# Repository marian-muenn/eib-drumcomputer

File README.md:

# EIB Drumcomputer

## Projektstruktur
~~~
Das Projekt ist wie folgt strukturiert:
  ./3d/                                                 Dateien für den 3D-Druck
  ./3d/abstandshalter_stromversorgung/                  Abstandhalter zur Montage der Stromversorgung
  ./3d/blindplatte/                                     Blindplatten in diversen Breiten
  ./3d/midi/                                            Frontplatte des MIDI-Interface-Moduls
  ./3d/modul-2-poti/                                    Frontplatte für Drummodule mit 2 Potentiometern
  ./3d/modul_3_poti/                                    Frontplatte für Drummodule mit 3 Potentiometern
  ./3d/winkel/                                          Winkel zur Platinenmontage
  ./doku/                                               Montageanleitung, Bauteillisten, Datenblätter und Spezifikationen
  ./kicad/                                              Platinenentwürfe
  ./kicad/midi-interface                                Platine des MIDI-Interface-Moduls
  ./kicad/line-out                                      Schaltplan des Line-Out Moduls
  ./kicad/klangerzeugung                                Platine zur Klangerzeugung
  ./ltspice/                                            Simulationen
  ./src                                                 Programmcode
  ./tex                                                 Latex Dokumente (Beleg und Montageanleitung)
~~~

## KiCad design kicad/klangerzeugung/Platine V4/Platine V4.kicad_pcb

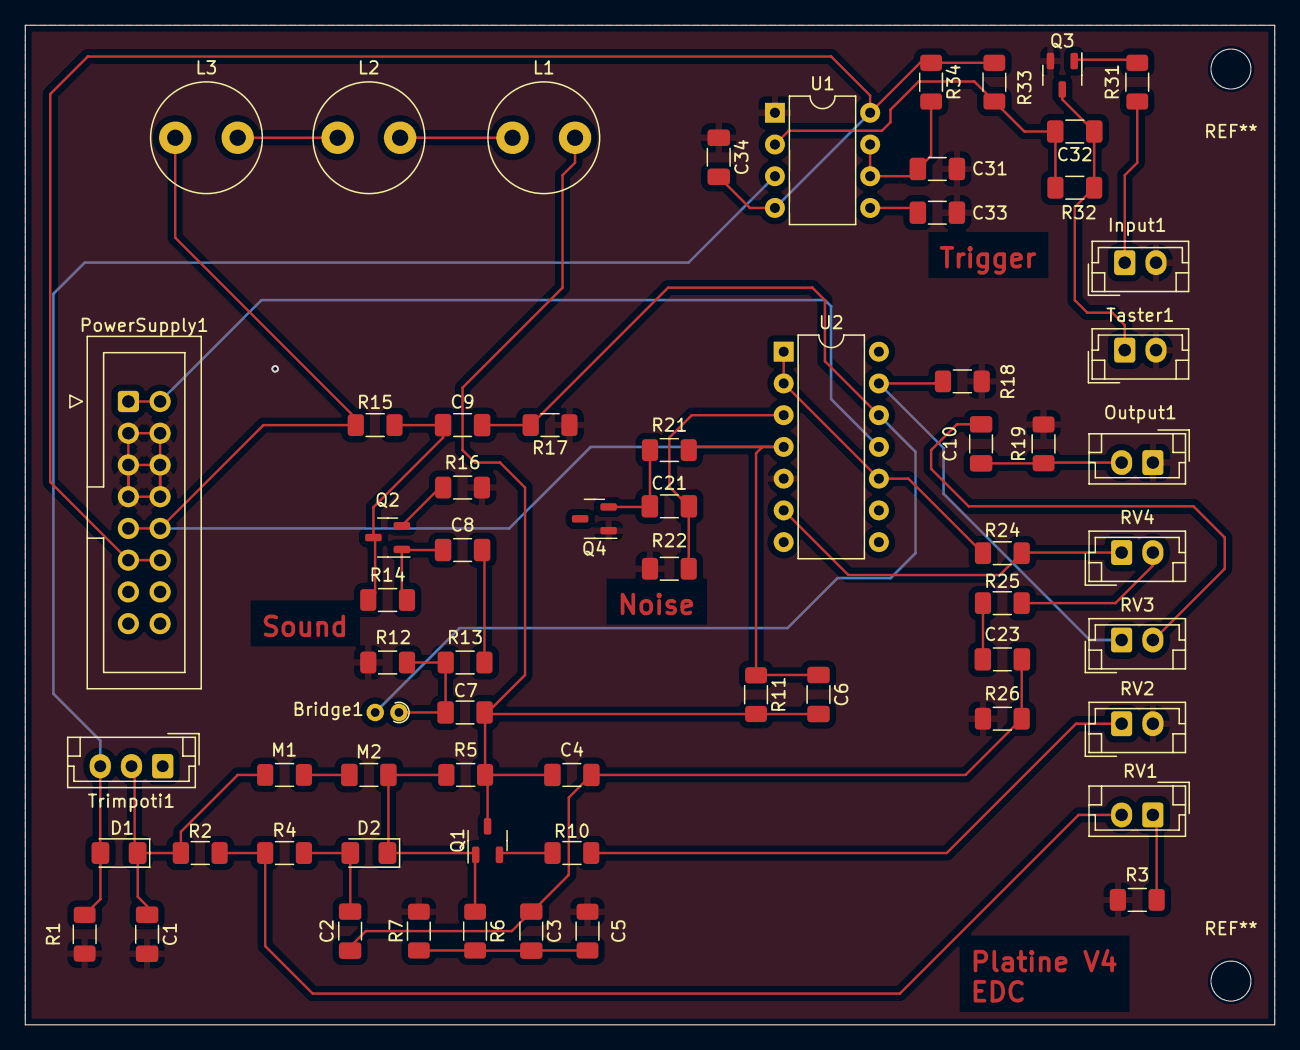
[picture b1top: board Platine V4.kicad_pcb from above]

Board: 2 copper layers, 100.0 x 80.0 mm, 65 parts (0 on the bottom side), 39 nets.

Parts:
Bridge1: 0; R_Axial_DIN0204_L3.6mm_D1.6mm_P1.90mm_Vertical
C1: 56n; C_1206_3216Metric_Pad1.33x1.80mm_HandSolder
C2, C4, C32: 10n; C_1206_3216Metric_Pad1.33x1.80mm_HandSolder
C3, C6: 1n; C_1206_3216Metric_Pad1.33x1.80mm_HandSolder
C5: 1000k; R_1206_3216Metric_Pad1.30x1.75mm_HandSolder
C7, C8, C9, C10, C21, C23: 1u; C_1206_3216Metric_Pad1.33x1.80mm_HandSolder
C31, C34: 100n; C_1206_3216Metric_Pad1.33x1.80mm_HandSolder
C33: 10u; C_1206_3216Metric_Pad1.33x1.80mm_HandSolder
D1: D; D_1206_3216Metric_Pad1.42x1.75mm_HandSolder
D2: D2; D_1206_3216Metric_Pad1.42x1.75mm_HandSolder
Input1: Conn_01x02_Pin; JST_EH_B2B-EH-A_1x02_P2.50mm_Vertical
L1, L2, L3: 100m; L_Radial_D8.7mm_P5.00mm_Fastron_07HCP
M1: 1M; R_1206_3216Metric_Pad1.30x1.75mm_HandSolder
M2: 82n; C_1206_3216Metric_Pad1.33x1.80mm_HandSolder
Output1: Conn_01x02_Pin; JST_EH_B2B-EH-A_1x02_P2.50mm_Vertical
PowerSupply1: Conn_02x08_Odd_Even; IDC-Header_2x08_P2.54mm_Vertical
Q1, Q2, Q3, Q4: Q_NPN_BEC; SOT-23-3
R1, R31, R34: 10k; R_1206_3216Metric_Pad1.30x1.75mm_HandSolder
R2, R3, R4, R7, R13, R14: 1000k; R_1206_3216Metric_Pad1.30x1.75mm_HandSolder
R5, R6: 470k; R_1206_3216Metric_Pad1.30x1.75mm_HandSolder
R10: 100; R_1206_3216Metric_Pad1.30x1.75mm_HandSolder
R11, R15: 1.5k; R_1206_3216Metric_Pad1.30x1.75mm_HandSolder
R12, R16, R17: 3k; R_1206_3216Metric_Pad1.30x1.75mm_HandSolder
R18, R19, R24, R26: 1k; R_1206_3216Metric_Pad1.30x1.75mm_HandSolder
R21, R22, R25: 100k; R_1206_3216Metric_Pad1.30x1.75mm_HandSolder
R32: 47k; R_1206_3216Metric_Pad1.30x1.75mm_HandSolder
R33: 220; R_1206_3216Metric_Pad1.30x1.75mm_HandSolder
RV1, RV2, RV4: 10k; JST_EH_B2B-EH-A_1x02_P2.50mm_Vertical
RV3: 50k; JST_EH_B2B-EH-A_1x02_P2.50mm_Vertical
Taster1: Conn_01x02_Pin; JST_EH_B2B-EH-A_1x02_P2.50mm_Vertical
Trimpoti1: 10k; JST_EH_B3B-EH-A_1x03_P2.50mm_Vertical
U1: NE555P; DIP-8_W7.62mm
U2: TL074; DIP-14_W7.62mm

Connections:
+5V: C34.2, PowerSupply1.11, PowerSupply1.12, R33.1, R34.1, U1.4 (R), U1.8 (VCC)
+12V: C6.1, L3.1, PowerSupply1.9, PowerSupply1.10, R11.1, R15.1, R21.1, U2.4 (V+)
-12V: PowerSupply1.1, PowerSupply1.2, U2.11 (V-)
GND: C1.2, C5.2, C31.1, C33.1, C34.1, Input1.2, Output1.1, PowerSupply1.3, PowerSupply1.4, PowerSupply1.5, PowerSupply1.6, PowerSupply1.7, PowerSupply1.8, Q3.2 (E), Q4.1 (B), R1.2, R3.1, R7.2, R12.1, R16.1, R17.1, R18.1, R19.2, R22.2, R26.2, RV2.2, Taster1.2, U1.1 (GND), U2.5 (+)
unnamed: Bridge1.1, C7.2, R12.2, R13.2
unnamed: C2.1, C3.1, C4.1, C23.2, R26.1
unnamed: C3.2, C5.1, R6.2, R7.1
unnamed: C8.1, R13.1
unnamed: C10.1, RV3.2
unnamed: C23.1, R25.2
unnamed: D1.2 (A), R1.1, Trimpoti1.3, U1.3 (Q)
unnamed: C1.1, D1.1 (K), M1.1, R2.1, Trimpoti1.2
unnamed: C2.2, D2.2 (A), R4.2
unnamed: D2.1 (K), M2.2, Q1.1 (B), R5.2, R6.1
unnamed: Input1.1, R31.1
unnamed: L1.1, L2.2
unnamed: L2.1, L3.2
unnamed: M1.2, M2.1
unnamed: C10.2, Output1.2, R19.1
unnamed: C4.2, C6.2, C7.1, L1.2, Q1.3 (C), R5.1, R11.2
unnamed: Q1.2 (E), R10.2
unnamed: C8.2, Q2.1 (B), R14.2
unnamed: C9.1, Q2.3 (C), R14.1, R15.2
unnamed: Q2.2 (E), R16.2
unnamed: Q3.1 (B), R31.2
unnamed: C32.1, Q3.3 (C), R32.2, Taster1.1
unnamed: C21.1, Q4.2 (E), R21.2
unnamed: R2.2, R4.1, RV1.2
unnamed: R3.2, RV1.1
unnamed: R10.1, RV2.1
unnamed: R25.1, RV4.2
unnamed: C33.2, U1.5 (CV)
unnamed: C31.2, R34.2, U1.6 (THR), U1.7 (DIS)
unnamed: C32.2, R32.1, R33.2, U1.2 (TR)
unnamed: C21.2, R22.1, U2.3 (+)
unnamed: R24.1, U2.1, U2.2 (-), U2.10 (+)
unnamed: R24.2, RV4.1, U2.6 (-)
unnamed: Bridge1.2, C9.2, R17.2, U2.12 (+)
unnamed: R18.2, RV3.1, U2.13 (-)

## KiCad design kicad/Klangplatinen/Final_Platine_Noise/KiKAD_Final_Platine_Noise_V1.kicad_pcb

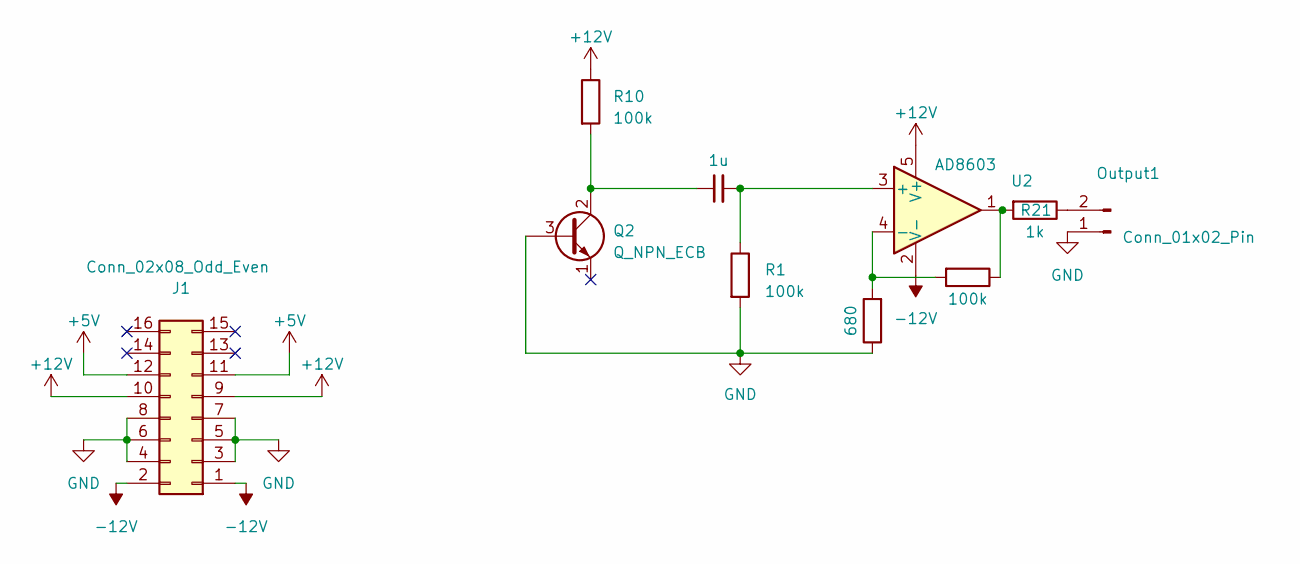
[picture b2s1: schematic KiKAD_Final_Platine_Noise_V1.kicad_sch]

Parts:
C1: 1u; C_1206_3216Metric_Pad1.33x1.80mm_HandSolder
J1: Conn_02x08_Odd_Even; IDC-Header_2x08_P2.54mm_Vertical_SMD
Output1: Conn_01x02_Pin; JST_EH_S2B-EH_1x02_P2.50mm_Horizontal
Q2: Q_NPN_ECB; SOT-23-3
R1, R2, R10: 100k; R_1206_3216Metric_Pad1.30x1.75mm_HandSolder
R20: 680; R_1206_3216Metric_Pad1.30x1.75mm_HandSolder
R21: 1k; R_1206_3216Metric_Pad1.30x1.75mm_HandSolder
U2: AD8603; TSOT-23-5

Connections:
+5V: J1.11, J1.12
+12V: J1.9, J1.10, R10.1, U2.5 (V+)
-12V: J1.1, J1.2, U2.2 (V-)
GND: J1.3, J1.4, J1.5, J1.6, J1.7, J1.8, Output1.1, Q2.3 (B), R1.2, R20.1
unnamed: Output1.2, R21.1
unnamed: C1.1, Q2.2 (C), R10.2
unnamed: R2.1, R21.2, U2.1
unnamed: C1.2, R1.1, U2.3 (+)
unnamed: R2.2, R20.2, U2.4 (-)

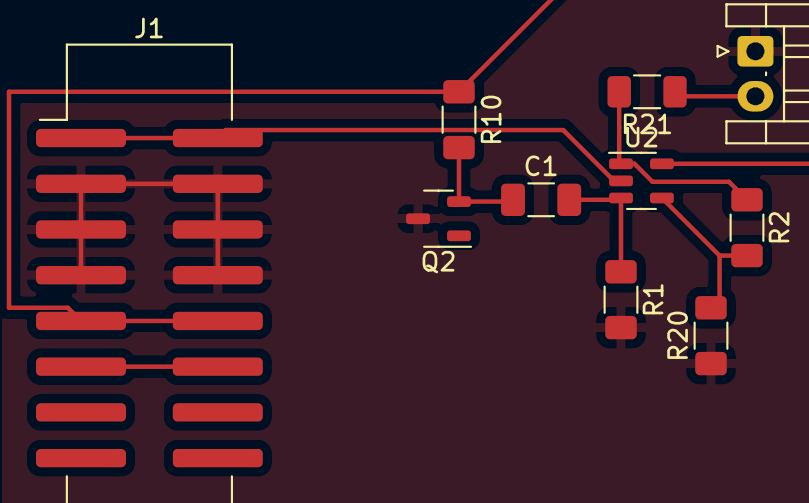
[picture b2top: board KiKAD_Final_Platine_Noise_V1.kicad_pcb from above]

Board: 2 copper layers, 10 parts (0 on the bottom side), 9 nets.

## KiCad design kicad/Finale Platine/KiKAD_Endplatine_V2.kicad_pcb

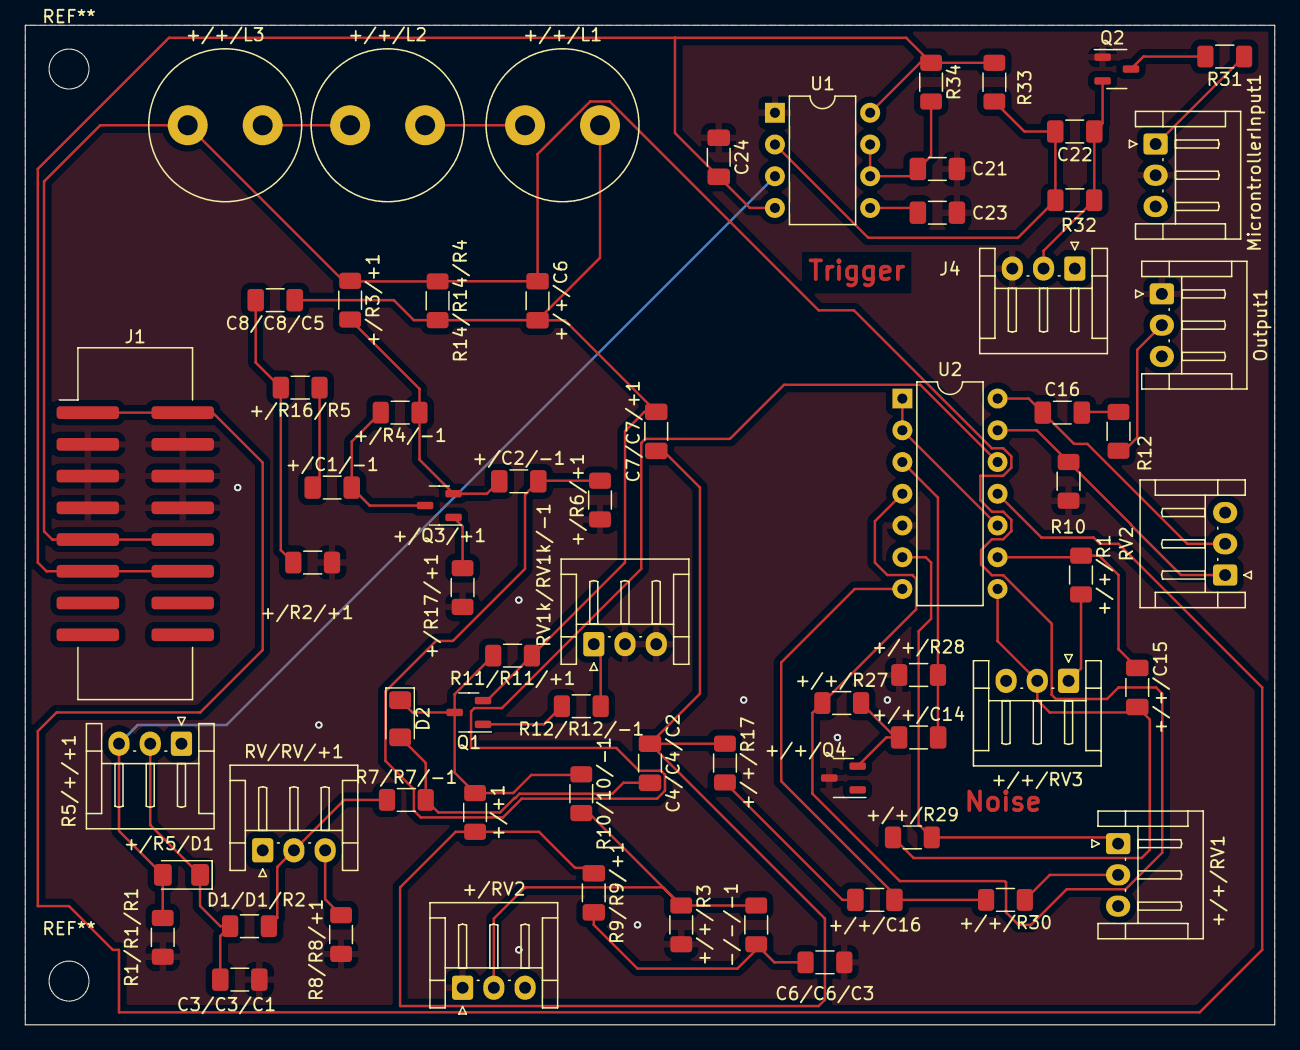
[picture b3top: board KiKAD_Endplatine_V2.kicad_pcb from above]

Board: 2 copper layers, 100.0 x 80.0 mm, 68 parts (0 on the bottom side), 44 nets.

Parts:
+/+1: 1000k; R_1206_3216Metric_Pad1.30x1.75mm_HandSolder
+/+/C6: 1n; C_1206_3216Metric_Pad1.33x1.80mm_HandSolder
+/+/C14, +/+/C16: 1u; C_1206_3216Metric_Pad1.33x1.80mm_HandSolder
+/+/C15: C; C_1206_3216Metric_Pad1.33x1.80mm_HandSolder
+/+/L1, +/+/L2, +/+/L3: 100m; L_Radial_D12.0mm_P6.00mm_Murata_1900R
+/+/Q4: Q_NPN_ECB; SOT-23-3
+/+/R1, +/+/R27, +/+/R28, +/+/R30: 100k; R_1206_3216Metric_Pad1.30x1.75mm_HandSolder
+/+/R3: 1000k; R_1206_3216Metric_Pad1.30x1.75mm_HandSolder
+/+/R17, +/+/R29: 1k; R_1206_3216Metric_Pad1.30x1.75mm_HandSolder
+/+/RV1, +/+/RV3: 10k; JST_EH_S3B-EH_1x03_P2.50mm_Horizontal
+/C1/-1, +/C2/-1: 1u; C_1206_3216Metric_Pad1.33x1.80mm_HandSolder
+/Q3/+1: Q_NPN_ECB; SOT-23-3
+/R2/+1, +/R6/+1, +/R17/+1: 3k; R_1206_3216Metric_Pad1.30x1.75mm_HandSolder
+/R3/+1: 1.5k; R_1206_3216Metric_Pad1.30x1.75mm_HandSolder
+/R4/-1, +/R16/R5: 1000k; R_1206_3216Metric_Pad1.30x1.75mm_HandSolder
+/R5/D1: D; D_1206_3216Metric_Pad1.42x1.75mm_HandSolder
+/RV2: 10k; JST_EH_S3B-EH_1x03_P2.50mm_Horizontal
-/-/-1: 1000k; R_1206_3216Metric_Pad1.30x1.75mm_HandSolder
C3/C3/C1: 56n; C_1206_3216Metric_Pad1.33x1.80mm_HandSolder
C4/C4/C2, C7/C7/+1: 10n; C_1206_3216Metric_Pad1.33x1.80mm_HandSolder
C6/C6/C3: 1000k; R_1206_3216Metric_Pad1.30x1.75mm_HandSolder
C8/C8/C5, C16: 1u; C_1206_3216Metric_Pad1.33x1.80mm_HandSolder
C21: 1p; C_1206_3216Metric_Pad1.33x1.80mm_HandSolder
C22, C24: 100n; C_1206_3216Metric_Pad1.33x1.80mm_HandSolder
C23: 10p; C_1206_3216Metric_Pad1.33x1.80mm_HandSolder
D1/D1/R2: 1000k; R_1206_3216Metric_Pad1.30x1.75mm_HandSolder
D2: C5/C5/D2; D_1206_3216Metric_Pad1.42x1.75mm_HandSolder
J1: Conn_02x08_Odd_Even; IDC-Header_2x08_P2.54mm_Vertical_SMD
J4: Conn_01x03_Pin; JST_EH_S3B-EH_1x03_P2.50mm_Horizontal
MicrontrollerInput1: Conn_01x02_Pin; JST_EH_S3B-EH_1x03_P2.50mm_Horizontal
Output1: Conn_01x02_Pin; JST_EH_S3B-EH_1x03_P2.50mm_Horizontal
Q1, Q2: Q_NPN_ECB; SOT-23-3
R1/R1/R1, R31, R32: 10k; R_1206_3216Metric_Pad1.30x1.75mm_HandSolder
R5/+/+1: 10k; JST_EH_S3B-EH_1x03_P2.50mm_Horizontal
R7/R7/-1: 1000k; R_1206_3216Metric_Pad1.30x1.75mm_HandSolder
R8/R8/+1: 5k; R_1206_3216Metric_Pad1.30x1.75mm_HandSolder
R9/R9/+1: 1n; C_1206_3216Metric_Pad1.33x1.80mm_HandSolder
R10, R12, R34: 1k; R_1206_3216Metric_Pad1.30x1.75mm_HandSolder
R10/10/-1, R11/R11/+1: 470k; R_1206_3216Metric_Pad1.30x1.75mm_HandSolder
R12/R12/-1: 100; R_1206_3216Metric_Pad1.30x1.75mm_HandSolder
R14/R14/R4: 1.5k; R_1206_3216Metric_Pad1.30x1.75mm_HandSolder
R33: 214; R_1206_3216Metric_Pad1.30x1.75mm_HandSolder
RV1k/RV1k/-1: 10k; JST_EH_S3B-EH_1x03_P2.50mm_Horizontal
RV2: 50k; JST_EH_S3B-EH_1x03_P2.50mm_Horizontal
RV/RV/+1: 10k; JST_EH_S3B-EH_1x03_P2.50mm_Horizontal
U1: NE555P; DIP-8_W7.62mm
U2: TL074; DIP-14_W7.62mm

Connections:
+5V: C24.2, J1.11, J1.12, R33.1, R34.1, U1.4 (R), U1.8 (VCC)
+12V: +/+/C6.1, +/+/L3.1, +/+/R27.1, +/R3/+1.1, J1.9, J1.10, R14/R14/R4.1, U2.4 (V+)
-12V: J1.1, J1.2, U2.11 (V-)
GND: +/+/Q4.3 (B), +/+/R3.2, +/+/R28.2, +/R2/+1.1, +/R6/+1.1, +/R17/+1.1, +/RV2.1, C3/C3/C1.2, C6/C6/C3.2, C21.1, C23.1, C24.1, J1.3, J1.4, J1.5, J1.6, J1.7, J1.8, J4.3, MicrontrollerInput1.2, Output1.1, Q2.1 (E), R1/R1/R1.2, R8/R8/+1.1, R10.1, RV1k/RV1k/-1.2, RV1k/RV1k/-1.3, U1.1 (GND), U2.5 (+)
unnamed: +/+/C15.2, +/+/R29.1, +/+/RV3.2, U2.8
unnamed: +/+/C16.1, +/+/R30.2, U2.7
unnamed: +/+/C16.2, +/+/R17.2
unnamed: +/+/L1.1, +/+/L2.2
unnamed: +/+/L2.1, +/+/L3.2
unnamed: +/+/C14.1, +/+/Q4.1 (E), +/+/R27.2
unnamed: +/+/R1.2, +/+/RV3.1
unnamed: +/+/R3.1, +/RV2.2, -/-/-1.1, R10/10/-1.2
unnamed: +/+1.2, +/+/R17.1, C4/C4/C2.1, C7/C7/+1.1, R9/R9/+1.1
unnamed: +/+/R30.1, +/+/RV1.2
unnamed: +/C1/-1.1, +/R16/R5.1
unnamed: +/C1/-1.2, +/Q3/+1.3 (B), +/R4/-1.2
unnamed: +/C2/-1.1, +/Q3/+1.2 (C), +/R3/+1.2, +/R4/-1.1
unnamed: +/Q3/+1.1 (E), +/R17/+1.2
unnamed: +/R5/D1.2 (A), R1/R1/R1.1, R5/+/+1.3, U1.3 (Q)
unnamed: +/R5/D1.1 (K), C3/C3/C1.1, D1/D1/R2.1, R5/+/+1.2
unnamed: +/R2/+1.2, +/R16/R5.2, C8/C8/C5.2
unnamed: -/-/-1.2, C6/C6/C3.1, R9/R9/+1.2
unnamed: C16.1, RV2.2, U2.14
unnamed: C16.2, R12.2
unnamed: D1/D1/R2.2, R7/R7/-1.1, RV/RV/+1.2
unnamed: C4/C4/C2.2, D2.2 (A), R7/R7/-1.2
unnamed: +/+1.1, D2.1 (K), Q1.3 (B), R10/10/-1.1, R11/R11/+1.2
unnamed: C22.1, J4.2, Q2.2 (C), R32.2
unnamed: MicrontrollerInput1.1, R31.1
unnamed: Output1.2, R12.1
unnamed: +/+/C6.2, +/+/L1.2, C7/C7/+1.2, C8/C8/C5.1, Q1.2 (C), R11/R11/+1.1, R14/R14/R4.2
unnamed: Q1.1 (E), R12/R12/-1.2
unnamed: Q2.3 (B), R31.2
unnamed: R8/R8/+1.2, RV/RV/+1.3
unnamed: R12/R12/-1.1, RV1k/RV1k/-1.1
unnamed: C23.2, U1.5 (CV)
unnamed: C21.2, R34.2, U1.6 (THR), U1.7 (DIS)
unnamed: C22.2, R32.1, R33.2, U1.2 (TR)
unnamed: +/+/C14.2, +/+/R28.1, U2.3 (+)
unnamed: U2.1, U2.2 (-), U2.10 (+)
unnamed: +/+/R29.2, +/+/RV1.1, U2.6 (-)
unnamed: +/+/C15.1, +/+/R1.1, U2.9 (-)
unnamed: +/C2/-1.2, +/R6/+1.2, U2.12 (+)
unnamed: R10.2, RV2.1, U2.13 (-)

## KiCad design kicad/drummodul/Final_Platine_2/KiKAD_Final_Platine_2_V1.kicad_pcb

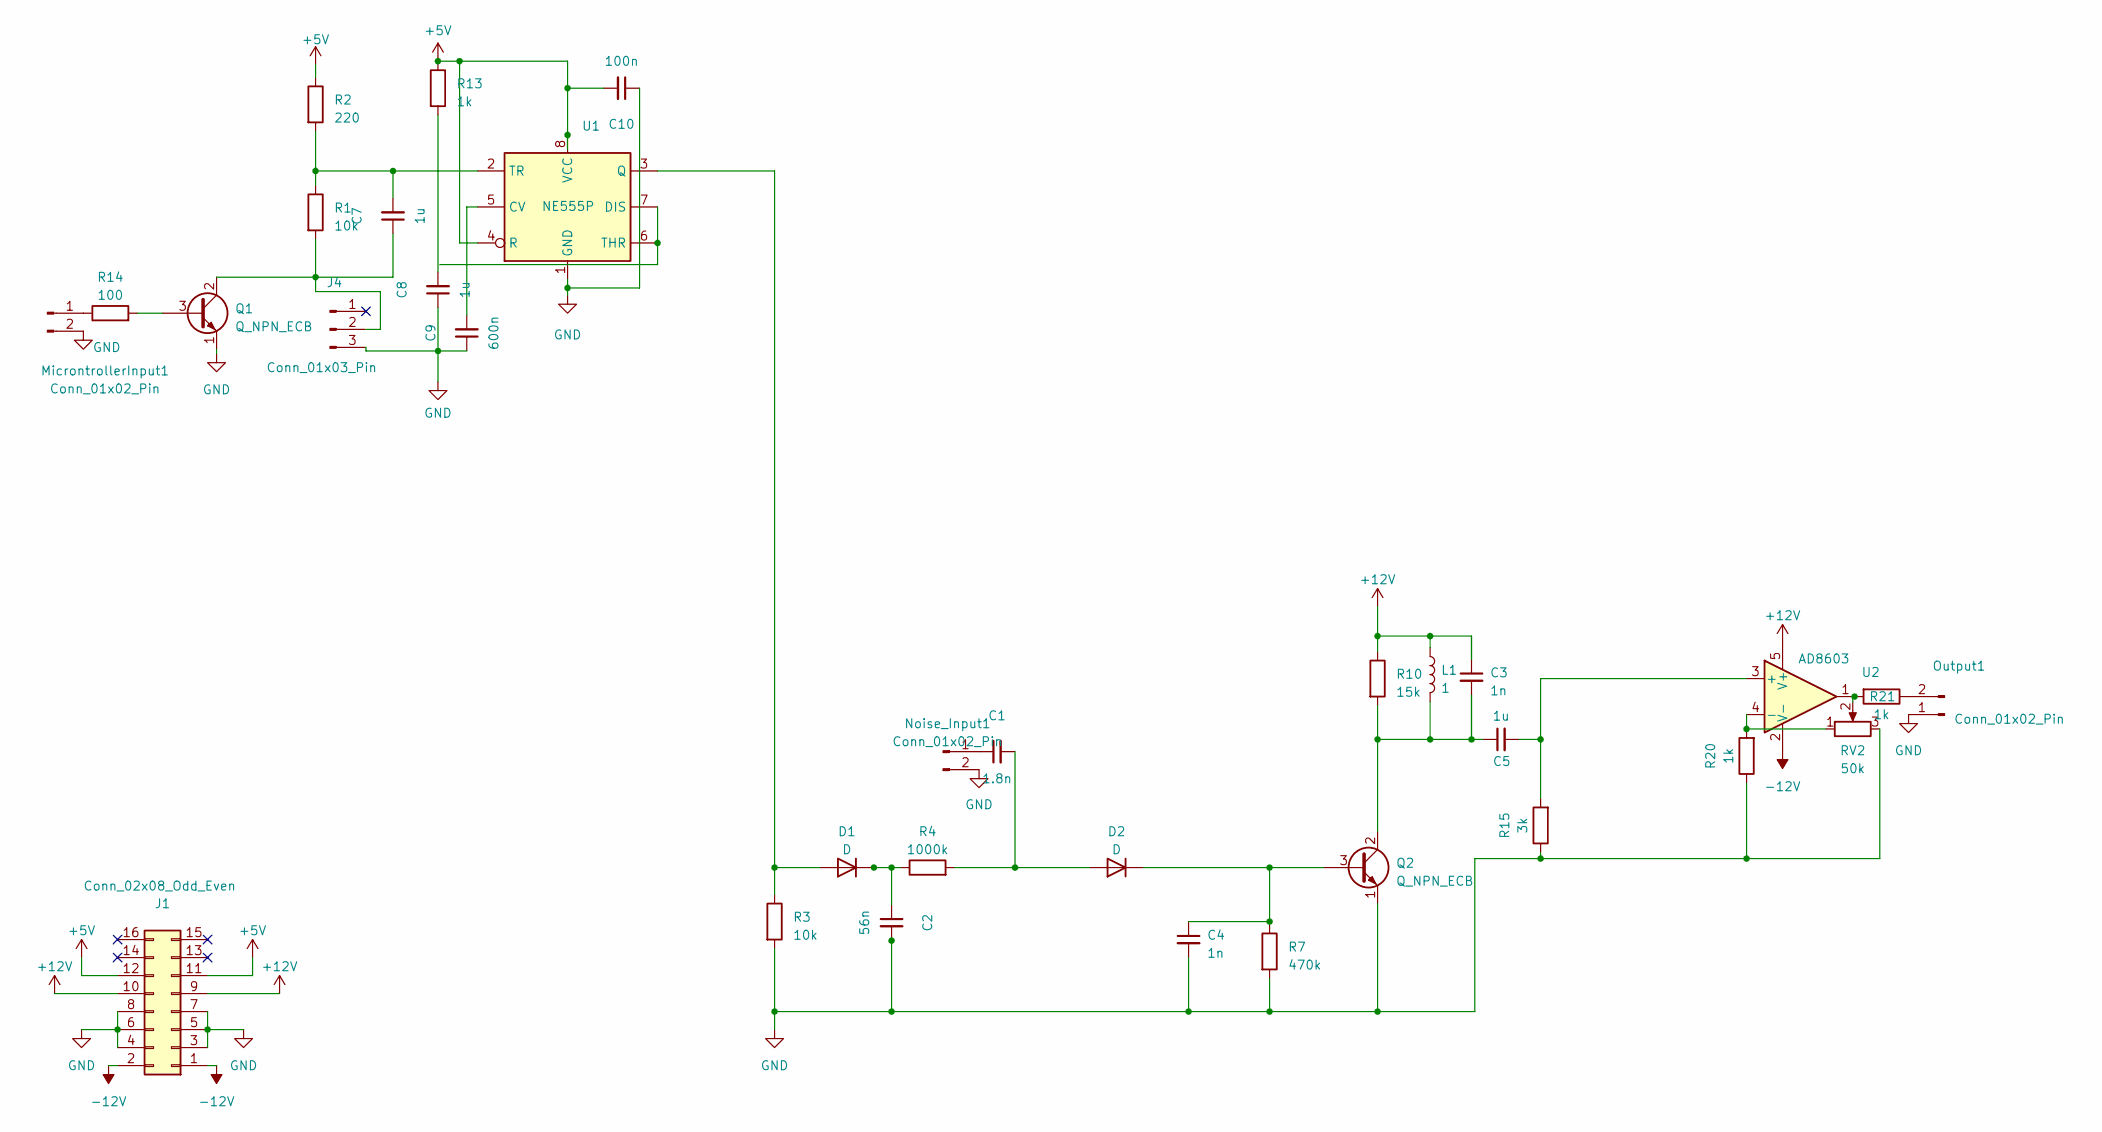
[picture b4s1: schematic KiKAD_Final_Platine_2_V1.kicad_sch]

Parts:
C1: 1.8n; C_1206_3216Metric_Pad1.33x1.80mm_HandSolder
C2: 56n; C_1206_3216Metric_Pad1.33x1.80mm_HandSolder
C3, C4: 1n; C_1206_3216Metric_Pad1.33x1.80mm_HandSolder
C5, C7, C8: 1u; C_1206_3216Metric_Pad1.33x1.80mm_HandSolder
C9: 600n; C_1206_3216Metric_Pad1.33x1.80mm_HandSolder
C10: 100n; C_1206_3216Metric_Pad1.33x1.80mm_HandSolder
D1, D2: D; D_1206_3216Metric_Pad1.42x1.75mm_HandSolder
J1: Conn_02x08_Odd_Even; IDC-Header_2x08_P2.54mm_Vertical_SMD
J4: Conn_01x03_Pin; JST_EH_S3B-EH_1x03_P2.50mm_Horizontal
L1: 1; L_1206_3216Metric_Pad1.42x1.75mm_HandSolder
MicrontrollerInput1: Conn_01x02_Pin; JST_EH_S2B-EH_1x02_P2.50mm_Horizontal
Noise_Input1: Conn_01x02_Pin; JST_EH_S2B-EH_1x02_P2.50mm_Horizontal
Output1: Conn_01x02_Pin; JST_EH_S2B-EH_1x02_P2.50mm_Horizontal
Q1, Q2: Q_NPN_ECB; SOT-23-3
R1, R3: 10k; R_1206_3216Metric_Pad1.30x1.75mm_HandSolder
R2: 220; R_1206_3216Metric_Pad1.30x1.75mm_HandSolder
R4: 1000k; R_1206_3216Metric_Pad1.30x1.75mm_HandSolder
R7: 470k; R_1206_3216Metric_Pad1.30x1.75mm_HandSolder
R10: 15k; R_1206_3216Metric_Pad1.30x1.75mm_HandSolder
R13, R20, R21: 1k; R_1206_3216Metric_Pad1.30x1.75mm_HandSolder
R14: 100; R_1206_3216Metric_Pad1.30x1.75mm_HandSolder
R15: 3k; R_1206_3216Metric_Pad1.30x1.75mm_HandSolder
RV2: 50k; JST_EH_S3B-EH_1x03_P2.50mm_Horizontal
U1: NE555P; DIP-8_W7.62mm
U2: AD8603; TSOT-23-5

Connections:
+5V: C10.2, J1.11, J1.12, R2.1, R13.1, U1.4 (R), U1.8 (VCC)
+12V: C3.1, J1.9, J1.10, L1.1, R10.1, U2.5 (V+)
-12V: J1.1, J1.2, U2.2 (V-)
GND: C2.2, C4.2, C8.1, C9.1, C10.1, J1.3, J1.4, J1.5, J1.6, J1.7, J1.8, J4.3, MicrontrollerInput1.2, Noise_Input1.2, Output1.1, Q1.1 (E), Q2.1 (E), R3.2, R7.2, R15.1, R20.1, RV2.3, U1.1 (GND)
unnamed: C8.2, R13.2
unnamed: D1.2 (A), R3.1, U1.3 (Q)
unnamed: C2.1, D1.1 (K), R4.1
unnamed: C1.2, D2.2 (A), R4.2
unnamed: C4.1, D2.1 (K), Q2.3 (B), R7.1
unnamed: C7.1, J4.2, Q1.2 (C), R1.2
unnamed: MicrontrollerInput1.1, R14.1
unnamed: C1.1, Noise_Input1.1
unnamed: Output1.2, R21.1
unnamed: Q1.3 (B), R14.2
unnamed: C3.2, C5.1, L1.2, Q2.2 (C), R10.2
unnamed: R21.2, RV2.2, U2.1
unnamed: C9.2, U1.5 (CV)
unnamed: U1.6 (THR), U1.7 (DIS)
unnamed: C7.2, R1.1, R2.2, U1.2 (TR)
unnamed: C5.2, R15.2, U2.3 (+)
unnamed: R20.2, RV2.1, U2.4 (-)

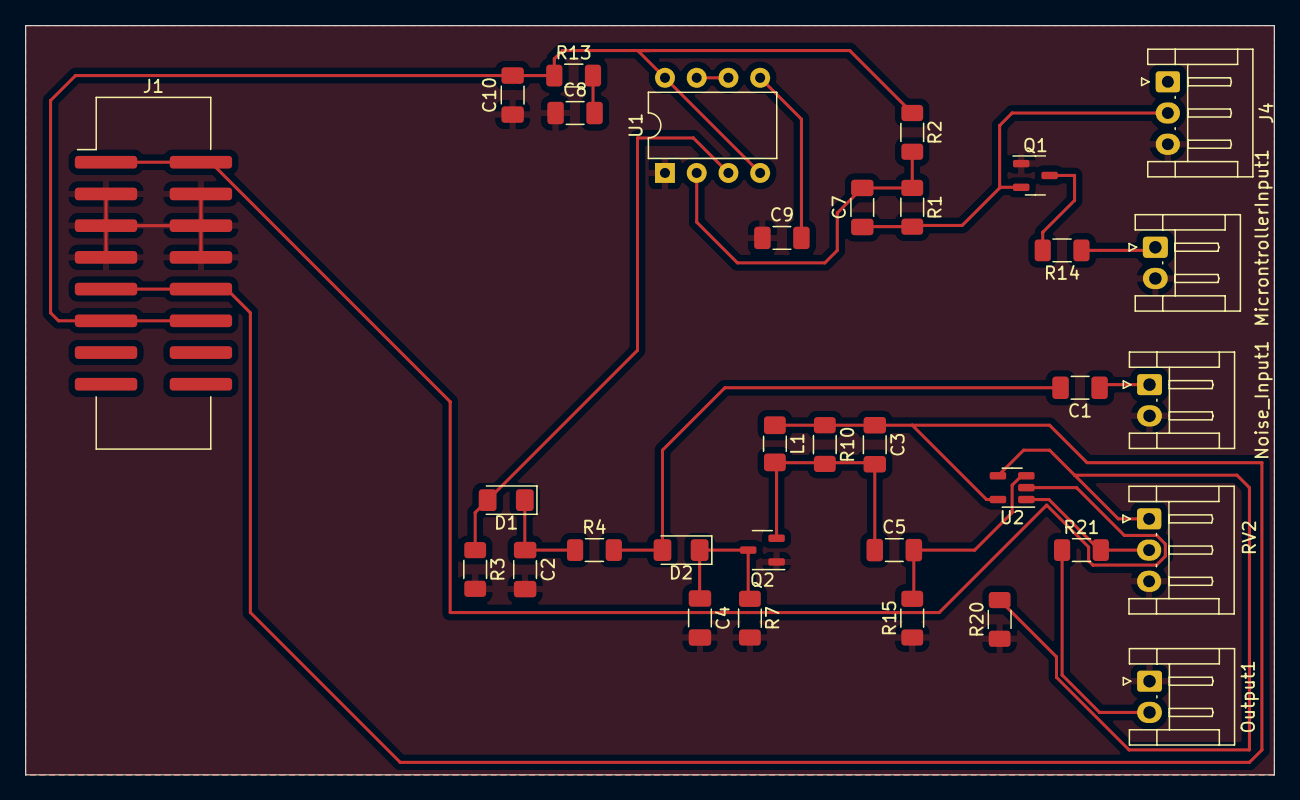
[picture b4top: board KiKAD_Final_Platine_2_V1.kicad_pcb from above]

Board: 2 copper layers, 100.0 x 60.0 mm, 33 parts (0 on the bottom side), 21 nets.

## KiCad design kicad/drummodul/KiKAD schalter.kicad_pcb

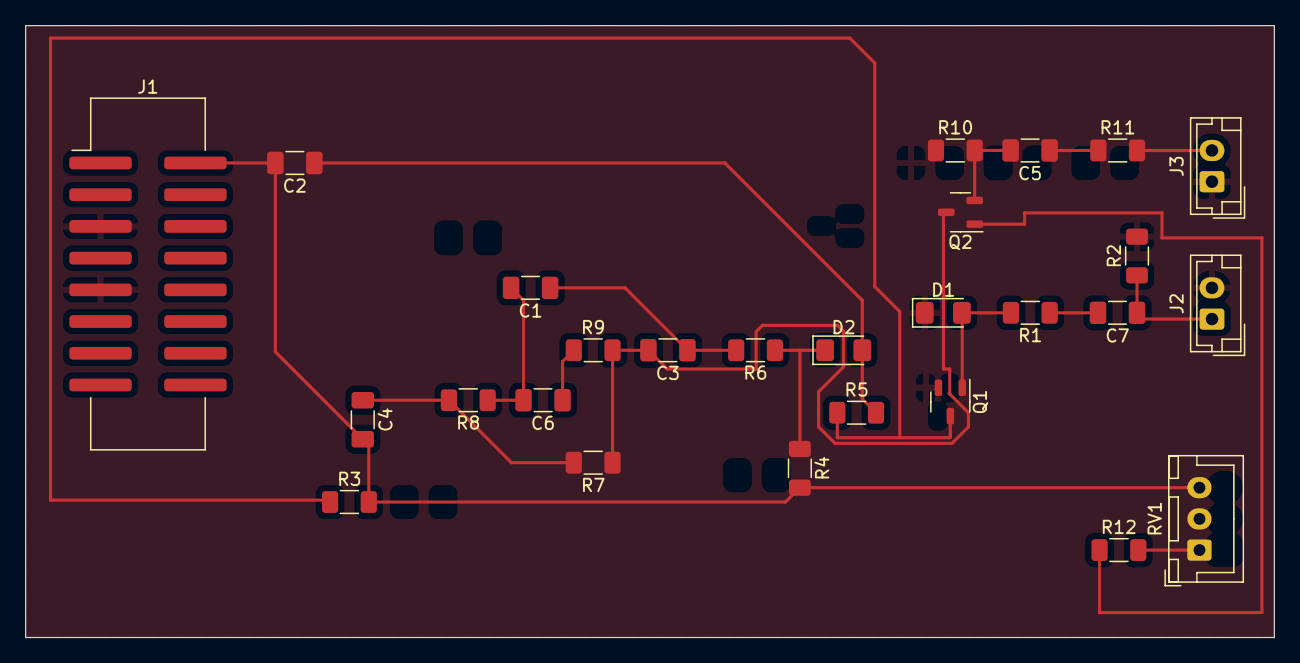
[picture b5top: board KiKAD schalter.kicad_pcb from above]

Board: 2 copper layers, 100.0 x 49.0 mm, 27 parts (0 on the bottom side), 18 nets.

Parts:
C1, C3, C7: 6.8n; C_1206_3216Metric_Pad1.33x1.80mm_HandSolder
C2: 10u; C_1206_3216Metric_Pad1.33x1.80mm_HandSolder
C4: 39n; C_1206_3216Metric_Pad1.33x1.80mm_HandSolder
C5: 0.47u; C_1206_3216Metric_Pad1.33x1.80mm_HandSolder
C6: 1u; C_1206_3216Metric_Pad1.33x1.80mm_HandSolder
D1, D2: D; D_1206_3216Metric_Pad1.42x1.75mm_HandSolder
J1: Conn_02x08_Odd_Even; IDC-Header_2x08_P2.54mm_Vertical_SMD
J2, J3: Conn_01x02_Pin; JST_EH_B2B-EH-A_1x02_P2.50mm_Vertical
Q1: Q_NPN_BCE; SOT-23-3
Q2: Q_NPN_ECB; SOT-23-3
R1, R2: 5.6k; R_1206_3216Metric_Pad1.30x1.75mm_HandSolder
R3: 100k; R_1206_3216Metric_Pad1.30x1.75mm_HandSolder
R4: 15k; R_1206_3216Metric_Pad1.30x1.75mm_HandSolder
R5: 330; R_1206_3216Metric_Pad1.30x1.75mm_HandSolder
R6: 8.2k; R_1206_3216Metric_Pad1.30x1.75mm_HandSolder
R7, R8: 27k; R_1206_3216Metric_Pad1.30x1.75mm_HandSolder
R9: 1000k; R_1206_3216Metric_Pad1.30x1.75mm_HandSolder
R10: 22k; R_1206_3216Metric_Pad1.30x1.75mm_HandSolder
R11: 560k; R_1206_3216Metric_Pad1.30x1.75mm_HandSolder
R12: 100; R_1206_3216Metric_Pad1.30x1.75mm_HandSolder
RV1: 1k; JST_XH_B3B-XH-A_1x03_P2.50mm_Vertical

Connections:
-12V: C2.2, C4.2, J1.2, R3.2, R4.2, RV1.2, RV1.3
GND: D1.1 (K), J1.5, J1.9, J2.2, J3.1, Q1.2 (C), R2.2, R10.1
unnamed: C1.1, C3.1, R6.2
unnamed: C1.2, C6.2, R8.1
unnamed: C4.1, R7.2, R8.2
unnamed: C5.1, R11.1
unnamed: C6.1, R9.1
unnamed: C7.2, R1.1
unnamed: D1.2 (A), Q1.1 (B), R1.2
unnamed: C2.1, D2.2 (A), R5.2
unnamed: D2.1 (K), R4.1, R6.1
unnamed: C7.1, J2.1, R2.1
unnamed: J3.2, R11.2
unnamed: Q1.3 (E), R3.1, R5.1
unnamed: C3.2, Q2.3 (B), R7.1, R9.2
unnamed: C5.2, Q2.2 (C), R10.2
unnamed: Q2.1 (E), R12.1
unnamed: R12.2, RV1.1

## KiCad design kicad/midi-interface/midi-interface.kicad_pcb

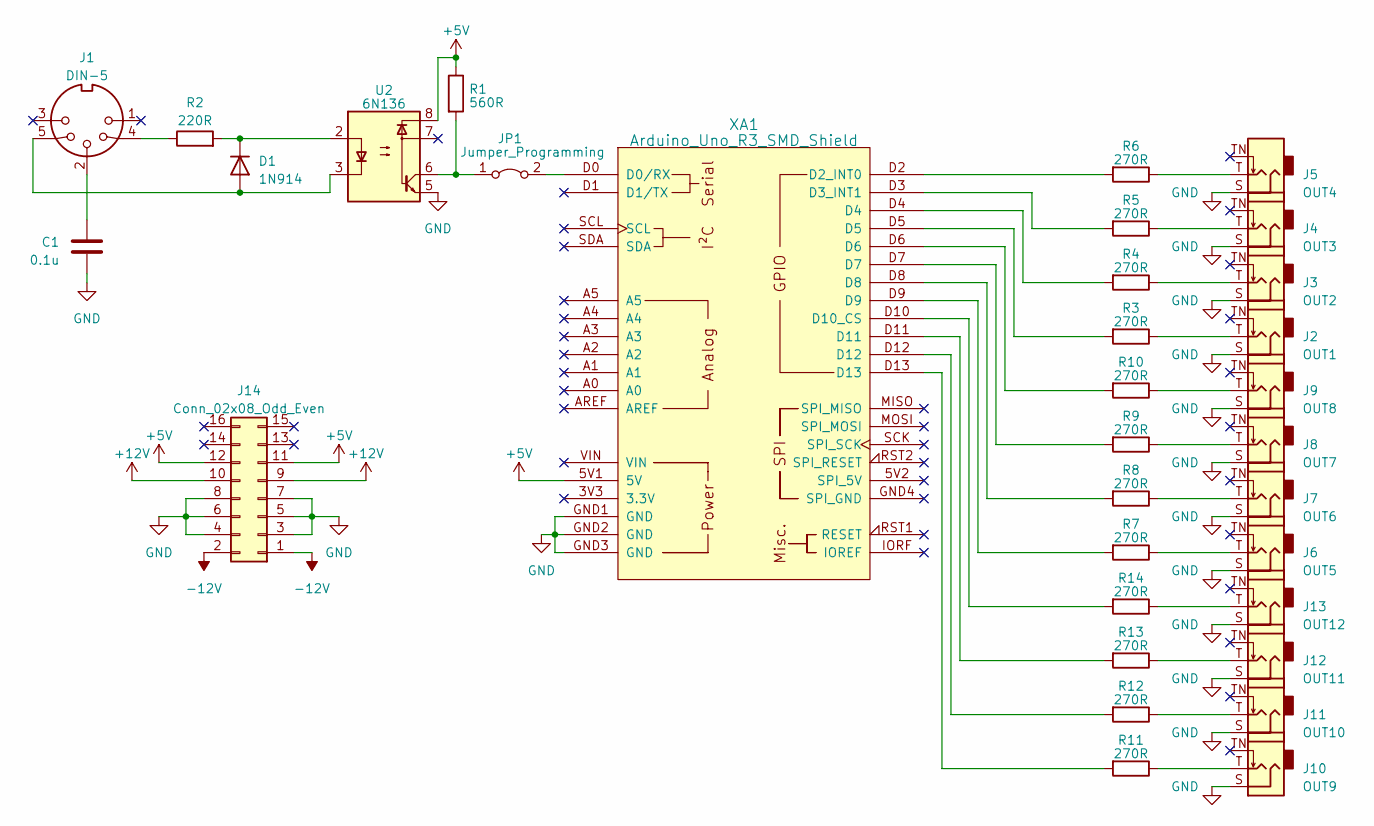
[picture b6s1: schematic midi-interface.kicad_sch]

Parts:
C1: 0.1u; C_1206_3216Metric_Pad1.33x1.80mm_HandSolder
D1: 1N914; D_DO-41_SOD81_P5.08mm_Vertical_AnodeUp
J1: DIN-5; PinHeader_1x05_P2.54mm_Vertical
J2: OUT1; Jack_3.5mm_QingPu_WQP-PJ398SM_Vertical_CircularHoles
J3: OUT2; Jack_3.5mm_QingPu_WQP-PJ398SM_Vertical_CircularHoles
J4: OUT3; Jack_3.5mm_QingPu_WQP-PJ398SM_Vertical_CircularHoles
J5: OUT4; Jack_3.5mm_QingPu_WQP-PJ398SM_Vertical_CircularHoles
J6: OUT5; Jack_3.5mm_QingPu_WQP-PJ398SM_Vertical_CircularHoles
J7: OUT6; Jack_3.5mm_QingPu_WQP-PJ398SM_Vertical_CircularHoles
J8: OUT7; Jack_3.5mm_QingPu_WQP-PJ398SM_Vertical_CircularHoles
J9: OUT8; Jack_3.5mm_QingPu_WQP-PJ398SM_Vertical_CircularHoles
J10: OUT9; Jack_3.5mm_QingPu_WQP-PJ398SM_Vertical_CircularHoles
J11: OUT10; Jack_3.5mm_QingPu_WQP-PJ398SM_Vertical_CircularHoles
J12: OUT11; Jack_3.5mm_QingPu_WQP-PJ398SM_Vertical_CircularHoles
J13: OUT12; Jack_3.5mm_QingPu_WQP-PJ398SM_Vertical_CircularHoles
J14: Conn_02x08_Odd_Even; IDC-Header_2x08_P2.54mm_Vertical
JP1: Jumper_Programming; PinHeader_1x02_P2.54mm_Vertical
R1: 560R; R_1206_3216Metric_Pad1.30x1.75mm_HandSolder
R2: 220R; R_1206_3216Metric_Pad1.30x1.75mm_HandSolder
R3, R4, R5, R6, R7, R8, R9, R10, R11, R12, R13, R14: 270R; R_1206_3216Metric_Pad1.30x1.75mm_HandSolder
U2: 6N136; DIP-8_W7.62mm
XA1: Arduino_Uno_R3_SMD_Shield; Arduino_Uno_R3_Shield

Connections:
+5V: J14.11, J14.12, R1.1, U2.8, XA1.5V1 (5V)
+12V: J14.9, J14.10
-12V: J14.1, J14.2
GND: C1.1, J2.S, J3.S, J4.S, J5.S, J6.S, J7.S, J8.S, J9.S, J10.S, J11.S, J12.S, J13.S, J14.3, J14.4, J14.5, J14.6, J14.7, J14.8, U2.5, XA1.GND1 (GND), XA1.GND2 (GND), XA1.GND3 (GND)
unnamed: C1.2, J1.2
unnamed: D1.2 (A), J1.5, U2.3
unnamed: D1.1 (K), R2.2, U2.2
unnamed: J1.4, R2.1
unnamed: J2.T, R3.1
unnamed: J3.T, R4.1
unnamed: J4.T, R5.1
unnamed: J5.T, R6.1
unnamed: J6.T, R7.1
unnamed: J7.T, R8.1
unnamed: J8.T, R9.1
unnamed: J9.T, R10.1
unnamed: J10.T, R11.1
unnamed: J11.T, R12.1
unnamed: J12.T, R13.1
unnamed: J13.T, R14.1
unnamed: JP1.1 (A), R1.2, U2.6
unnamed: JP1.2 (B), XA1.D0 (D0/RX)
unnamed: R3.2, XA1.D5
unnamed: R4.2, XA1.D4
unnamed: R7.2, XA1.D9
unnamed: R8.2, XA1.D8
unnamed: R9.2, XA1.D7
unnamed: R10.2, XA1.D6
unnamed: R11.2, XA1.D13
unnamed: R12.2, XA1.D12
unnamed: R13.2, XA1.D11
unnamed: R6.2, XA1.D2 (D2_INT0)
unnamed: R5.2, XA1.D3 (D3_INT1)
unnamed: R14.2, XA1.D10 (D10_CS)

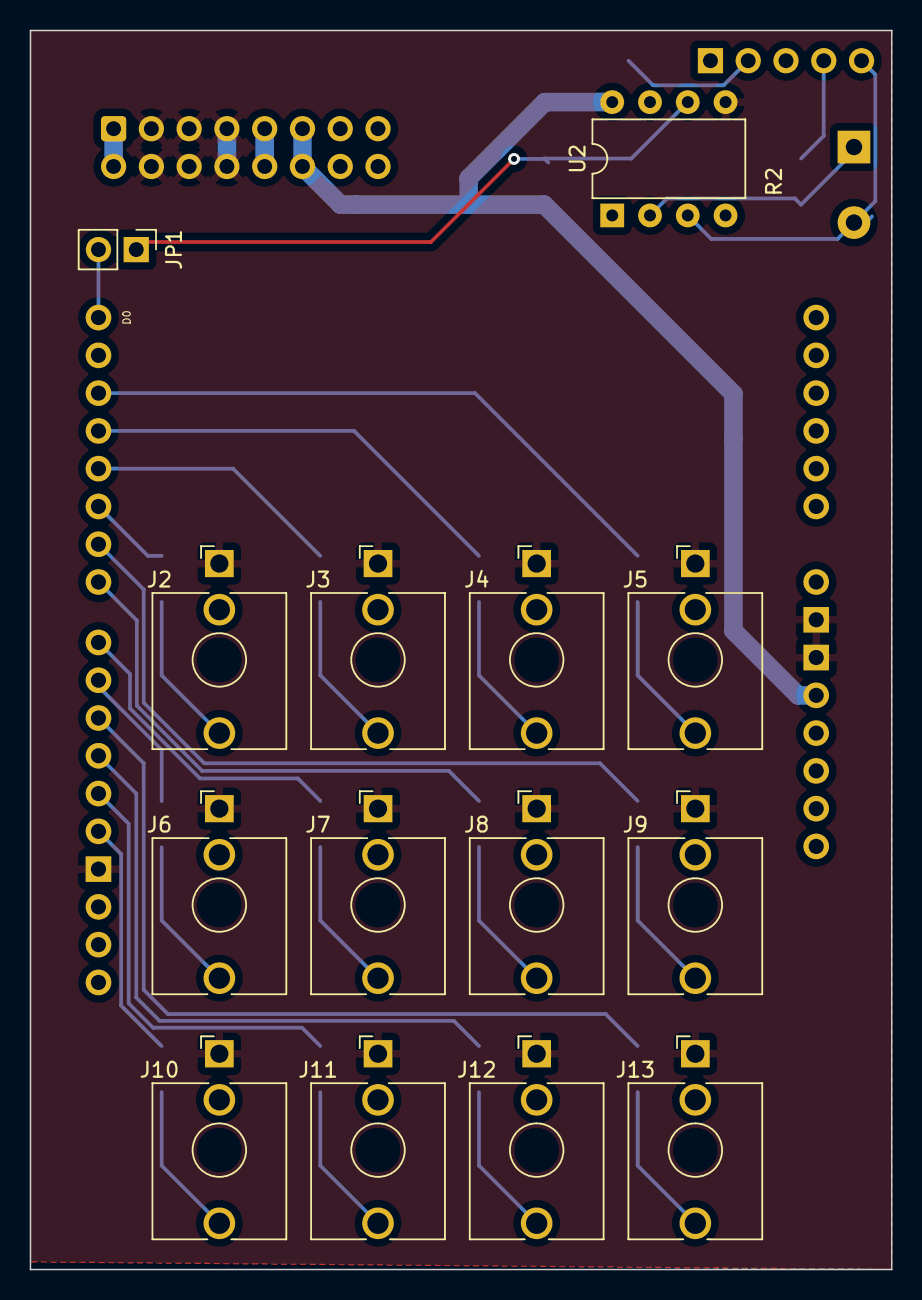
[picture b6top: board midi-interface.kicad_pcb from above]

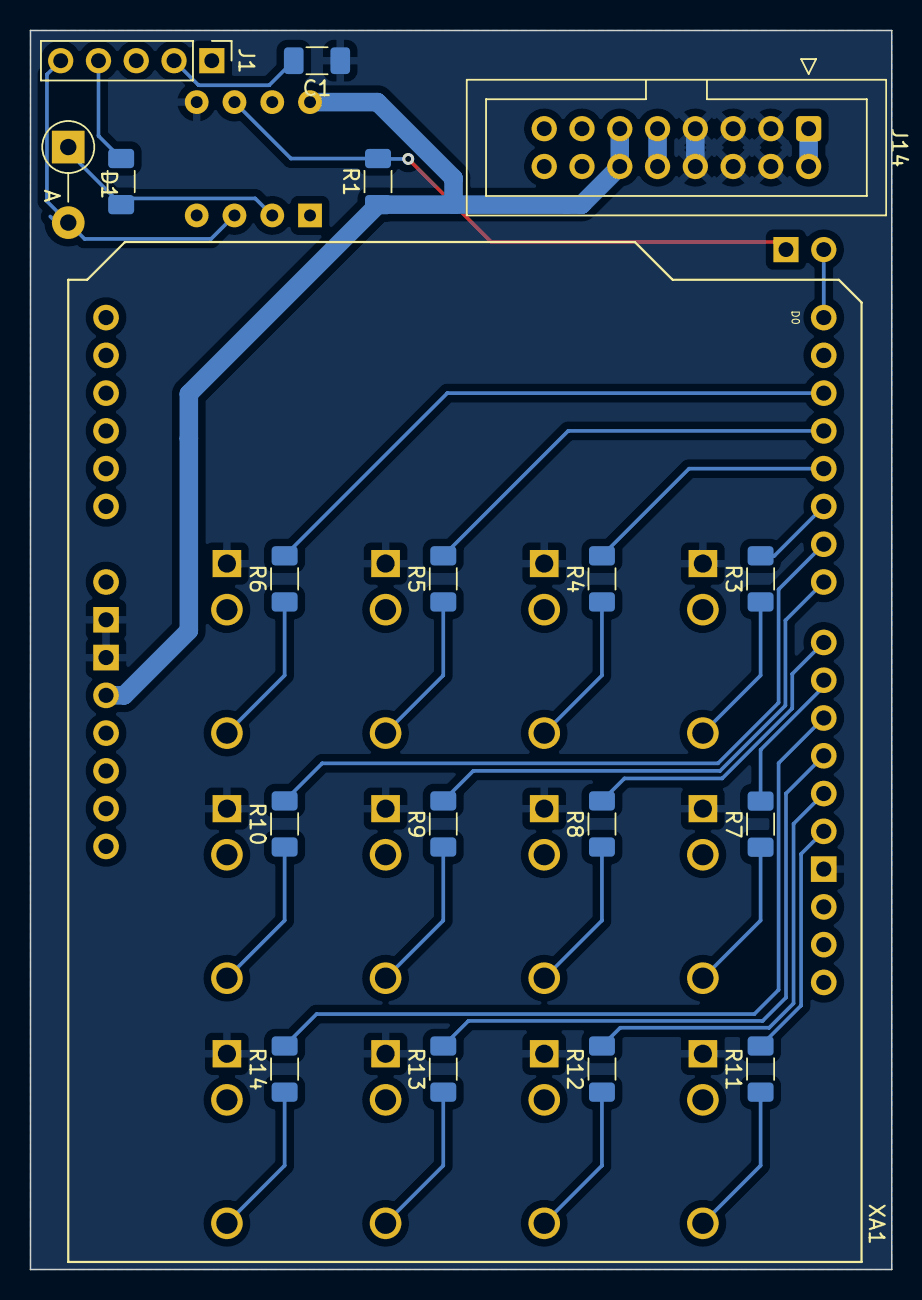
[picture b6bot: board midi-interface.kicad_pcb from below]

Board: 2 copper layers, 57.9 x 83.3 mm, 33 parts (18 on the bottom side), 34 nets.

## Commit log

2023-04-25 25.04
2023-04-26 snare
2023-04-27 fixed snare
2023-04-27 kicad midi, ltspice snare
2023-05-02 Yamaha D80 Bassdrum in LTSpice
2023-05-02 Spezifikation für platinendesign
2023-05-02 midi interface kicad update
2023-05-03 update midi interface layout
2023-05-04 midi interface Platinenlayout, frontplatte
2023-05-14 fertiggestellte midi Platine, Frontplatte für midi interface
2023-05-17 gehäuseabdeckung breiter
2023-05-17 Simulation der einzelnen Soundsynthesen und Aufteilung der Platinen
2023-05-21 frontplattev3
2023-05-23 line-out frontplatte
2023-05-24 testdatei angelegt zu demonstrationszwecken
2023-05-28 Revert "testdatei angelegt zu demonstrationszwecken"
    This reverts commit 51961437d5db1b91d120f40179090828b45779b3.
2023-05-31 added dot file for MIDI State machine
2023-05-31 Erster Platinenentwurf
    Erster Platinenentwurf, ohne Tasterschaltung
2023-05-31 drummodul schaltplan angepasst
2023-06-01 added latex template
2023-06-01 Readme überarbeitet
2023-06-01 c code
2023-06-03 Finales Platinen Updatet
2023-06-05 Progress in KiCad
    Habe Neue Ordner Erstellt, wo die einzelnen Platinen drin sind. Bisher habe ich alle Schaltungen in KiCad aufgebaut,
    das PlatinenDesign kommt heute Abend
2023-06-06 Platinen sind Ready
2023-06-07 midi src
2023-06-15 Finales Update LT-Spice
2023-06-20 Platine (unfertig)
2023-06-22 finales update lt spice
2023-06-22 finales update
2023-06-23 Platinendesign update mit 2 Induktoren
2023-06-25 Platinenupdate
    Platine geupdatet Beschriftung mehr oder weniger gut
2023-06-27 Schaltplan verschönert
2023-06-28 Namenochmal geupdated
2023-06-28 ultra finales update
2023-06-28 kicad überarbeitung
2023-06-28 noch endgültigere finalplatine
2023-06-30 PLATINE endlich fertig glaube ich
2023-07-08 Beschriftung verändert
2023-08-25 software entwurf 1
2023-09-11 alles mögliche
2023-09-11 kleines Platinenupdate
2023-09-12 Sachen gelöscht
    Alte Kicad Projekte gelöscht
    s
2023-09-12 aufräumaktion
2023-09-12 diverse scad dateien
2023-09-12 deleted desktop.ini
2023-09-12 aufgeräumt, README aktualisiert
2023-09-14 Summierer hinzugefügt
2023-09-14 ergänzung summierer
2023-09-15 neue beschriftung in KiCad
2023-09-15 Anfang von Bautteilliste
2023-09-16 3DP Modules
2023-09-16 Bautteilliste Update
    Neue Bautteilliste jtzt in Doku Ordner
    KiCad Namensstruktur verändert und jaaa
2023-09-16 Readme, state machine
2023-09-16 jetzt hoffentlich
2023-09-17 Add files via upload
    LT Spice Simulation
2023-09-17 beleg
2023-09-17 aufgeräumt
2023-09-17 Montageanleitung
2023-09-17 abgabe
2023-09-23 latest update
2023-09-23 Schaltungsplan Update
    Massebezug hergestellt, update zu Footprints
2023-09-23 Update 2 zu Platinen
2023-09-25 Neues Platinendesign
    Neues Platinendesign
    - Angenehmeres Design
    - Drahtbrücken in Schaltung inbegriffen
    - Bessere Footprints
2023-09-25 Platinenbeschriftung
    Jetzt auch mit einer Platinen Beschriftung:
    Platine 4
    EDC (EIB DrumComputer)
